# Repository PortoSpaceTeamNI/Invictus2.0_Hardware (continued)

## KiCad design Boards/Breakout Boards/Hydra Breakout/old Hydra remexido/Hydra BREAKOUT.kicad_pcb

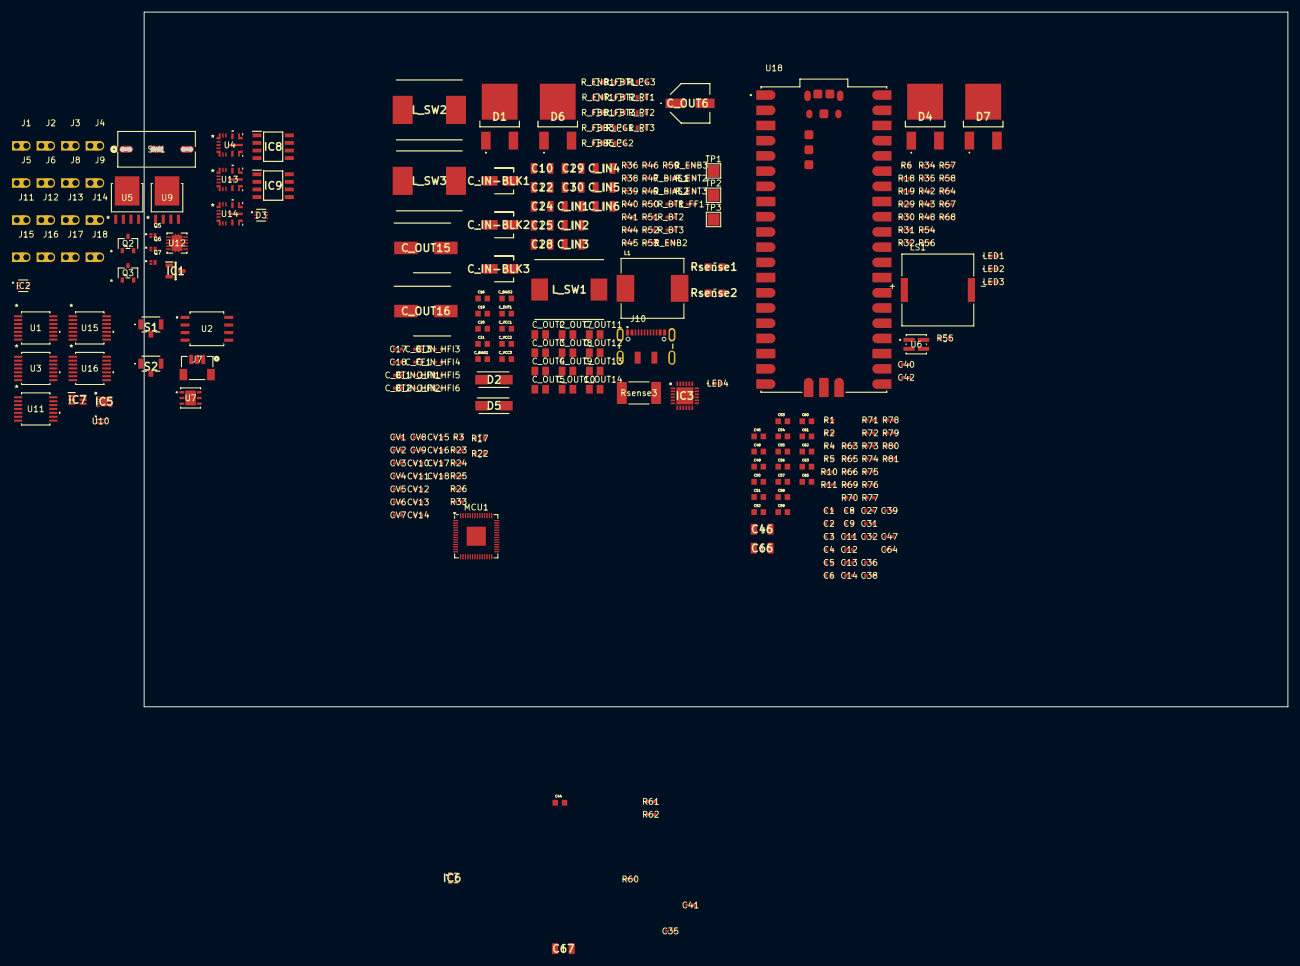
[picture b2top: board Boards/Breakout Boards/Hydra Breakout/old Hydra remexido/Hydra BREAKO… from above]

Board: 4 copper layers, 194.6 x 116.0 mm, 282 parts (0 on the bottom side), 160 nets, no tracks yet.

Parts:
C1, C3, C4, C5, C8, C9, C11, C13, C14, C17, C18, C27, C35, C36, C40, C41, C42, C47, C64: 100n; Capacitor_0402
C2, C6, C12, C31, C32, C39: 10n; Capacitor_0402
C10, C24, C25, C28: 2.2u; Capacitor_1206
C16, C19, C20, C21, C44, C45, C65: 1u; Capacitor_0603
C22, C46, C66, C67: 4.7u; Capacitor_1206
C29, C30: 470n; Capacitor_1206
C38: 100nF; Capacitor_0402
C48, C51, C53, C55, C60, C61, C62, C63: 22n; Capacitor_0603
C49, C50, C52, C54, C56, C57, C58, C59: 27n; Capacitor_0603
CV1, CV3, CV6, CV16, CV17: 1uF; Capacitor_0402
CV2, CV4, CV5, CV7, CV8, CV9, CV10, CV11, CV12, CV13, CV18: 100nF; Capacitor_0402
CV14, CV15: 4.7uF; Capacitor_0402
C_BIAS1, C_BIAS2: 1u; Capacitor_0603
C_BT1, C_BT2, C_BT3: 100n; Capacitor_0402
C_FF1: 22p; Capacitor_0402
C_IN1, C_IN2, C_IN3, C_IN4, C_IN5, C_IN6: 4.7u; Capacitor_1206
C_IN-BLK1, C_IN-BLK2, C_IN-BLK3: 10u; Capacitor_4mm
C_IN_HFI1, C_IN_HFI2, C_IN_HFI3, C_IN_HFI4, C_IN_HFI5, C_IN_HFI6: 100n; Capacitor_0402
C_OUT1: 1u; Capacitor_0603
C_OUT2, C_OUT3, C_OUT4, C_OUT5: 10u; Capacitor_0805
C_OUT6: 100u; Capacitor_6mm
C_OUT7, C_OUT8, C_OUT11, C_OUT12, C_OUT13, C_OUT14: 22u; Capacitor_0805
C_OUT9, C_OUT10: 47u; Capacitor_0805
C_OUT15: 560u; Capacitor_8mm
C_OUT16: 100u; Capacitor_8mm
C_VCC1, C_VCC2, C_VCC3: 1u; Capacitor_0603
D1, D6: RB095BGE; RD3P175SNFRATL
D2, D5: RSX301L; DIOM5026X220N
D3: SP3004-04XTG; SOT563_LTF
D4, D7: RB095BGE-30TL; RD3P175SNFRATL
IC1: BC846BLT1G; SOT96P237X111-3N
IC2: NSVT30010MXV6T1G; SOT-563_1P3X1P7_ONS
IC3: CYPD3177-24LQXQT; QFN50P400X400X60-25N-D
IC5: INA2181A4IDSQR; SON40P200X200X80-11N
IC6: PCA9306GM,125; PCA9570GMH
IC7: INA181A4QDCKRQ1; SOT65P210X110-6N
IC8, IC9: DMP2040USD-13; SOIC127P600X175-8N
J1, J2, J3, J4, J5, J6, J8, J9, J11, J12, J13, J14, J15, J16, J17, J18: Conn_01x01_Socket; Pico_01pin
J7: BM03B-SRSS-TBLFSN; CONN_BM03B-SRSS-TBLFSN_JST
J10: DX07S016JA1R1500; JAE_DX07S016JA1R1500
L1: 2.2u; IND_SPM10065VT-2R2M-D
LED1, LED2, LED3, LED4: VLMS1500-GS08; LED_00-GS08_VIS_RED
LS1: PKLCS1212E20A0-R1
L_SW1: 10u; Inductor_11.5x10
L_SW2, L_SW3: 15u; Inductor_10.1x10
MCU1: RP2040; QFN-56-1EP_7x7mm_P0.4mm_EP3.2x3.2mm
Q2, Q3: 2N7002H6327XTSA2; PG-SOT23-3-5_INF_MIN
Q5, Q6, Q7: BC857CMB_315; TRANS_PMZB550UNEYL
R1, R2, R4, R5, R10, R11, R23, R24, R29, R32, R34, R64, R67: 100; RES_0402
R3, R18, R19, R25, R26, R52, R53, R61, R62, R63, R65, R66, R69, R70, R71, R72, R73, R74, R75, R76, R77, R78, R79, R80, R81: 1k; RES_0402
R6, R30, R33, R48, R51, R68: 10k; RES_0402
R17, R22: 27; RES_0603
R31: 150; RES_0402
R35, R36, R38, R39, R40, R41, R43, R44, R45, R46, R57, R58: 2k; RES_0402
R42: 65; RES_0402
R47: DNP; RES_0402
R49, R50: 50k; RES_0402
R54: 320; RES_0402
R55: 120; RES_0603
R56: 500; RES_0402
R59: 95; RES_0402
R60: 200k; RES_0402
R_BIAS1, R_BIAS2: 5; RES_0402
R_BT1, R_BT2: 50; RES_0402
R_BT3: 100; RES_0402
R_ENB1: 100k; RES_0603
R_ENB2: 63k4; RES_0402
R_ENB3: 45k3; RES_0402
R_ENT1: 931k; RES_0603
R_ENT2: 590k; RES_0402
R_ENT3: 422k; RES_0402
R_FBB1: 8k66; RES_0603
R_FBB3: 12k7; RES_0603
R_FBB5: 22k1; RES_0603
R_FBT1, R_FBT2, R_FBT3: 100K; RES_0603
R_FF1: 1k; RES_0402
R_PG1, R_PG2, R_PG3: 100K; RES_0603
R_RT1, R_RT2, R_RT3: 33k2; RES_0603
Rsense1, Rsense2: 2.5m; RES_0805
Rsense3: 20m; RES_WSLP2512
S1, S2: TL1017AABF160QG
SW1: D2F-01-D; D2F-01-D_OMR
TP1, TP2, TP3: TestPoint; TestPoint_Pad_2.0x2.0mm
U1, U3, U11: MAX31856MUD+T; 21-0066J_14_MXM
U2: W25Q128JVSIQ TR; SOIC_208MIL_WIN
U4, U13, U14: LM61460AASQRJRRQ1; VQFN-HR14_RJR_TEX
U5, U9: SQJA36EP-T1_GE3; PowerPAK_SO-8L_3_VIS
U6: VLMKG3400-GS08; SMT_00-GS08_VIS
U7: ST1L05APU33R; DFN_5APU33R_STM
U10: STLM20DD9F; UDFN-4L_STM
U12: THVD2410VDRCR; VSON10_DRC_TEX
U15, U16: AD8040ARUZ; RU_14_ADI
U18: SC0915; MODULE_SC0915

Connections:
+3.3V: C3.2, C4.2, C8.2, C9.2, C13.2, C14.2, C17.1, C18.1, C19.1, C38.1, C41.1, C42.2, CV5.1, CV6.1, CV7.1, CV8.1, CV9.1, CV10.1, CV11.1, CV12.1, CV13.1, CV15.2, CV17.1, CV18.1, IC3.5 (ISNK_COARSE), IC3.23 (VDDD), IC6.2 (VREF1), MCU1.1 (IOVDD), MCU1.10 (IOVDD), MCU1.22 (IOVDD), MCU1.33 (IOVDD), MCU1.42 (IOVDD), MCU1.43 (ADC_AVDD), MCU1.44 (VREG_IN), MCU1.48 (USB_VDD), MCU1.49 (IOVDD), Q2.1 (G), Q3.1 (G), R3.1, R33.2, R39.1, R40.1, R41.1, R43.1, R44.2, R45.2, R47.2, R48.1, R58.1, U1.5 (AVDD), U1.8 (DVDD), U2.8 (VCC), U3.5 (AVDD), U3.8 (DVDD), U7.2 (V0), U10.4 (VCC), U11.5 (AVDD), U11.8 (DVDD), U12.1 (VIO)
+5V: C27.1, C36.1, C40.1, C44.1, C67.1, CV14.2, CV16.2, D3.5 (VCC), IC5.10 (VS), IC7.3 (VS), IC7.5 (IN-), IC9.5 (D2), IC9.6 (D2), LED1.2, LED2.2, LED3.2, LED4.2, LS1.P, R19.1, R35.1, R57.1, R60.2, R61.1, R62.1, Rsense3.2, SW1.2, U6.1 (C_RED), U6.3 (C_Green), U7.3 (V1), U12.10 (VCC)
+8.4V: C45.1, C46.1, C47.2, C64.2, C65.1, C66.1, IC5.8 (IN-2), J17.1, Rsense2.2, U15.4 (+VS), U16.4 (+VS)
+12V: D4.2, D7.2, IC5.2 (IN-1), J18.1, Rsense1.2
/1~DRDY THERMO: MCU1.9 (GPIO7), U1.7 (~DRDY)
/1~FAULT THERMO: MCU1.15 (GPIO12), Q5.1, U1.13 (~FAULT)
/2~DRDY THERMO: MCU1.27 (GPIO16), U11.7 (~DRDY)
/2~FAULT THERMO: MCU1.28 (GPIO17), Q6.1, U11.13 (~FAULT)
/3~DRDY THERMO: MCU1.29 (GPIO18), U3.7 (~DRDY)
/3~FAULT THERMO: MCU1.30 (GPIO19), Q7.1, U3.13 (~FAULT)
/ENABLE_RS: MCU1.8 (GPIO6), R30.1, U12.3 (DE), U12.4 (~RE)
/Green Status: IC2.2 (B2), MCU1.37 (GPIO25)
/MISO SPI: MCU1.13 (GPIO10), U1.11 (SDO), U3.11 (SDO), U11.11 (SDO)
/MOSI SPI: MCU1.14 (GPIO11), U1.12 (SDI), U3.12 (SDI), U11.12 (SDI)
/Main Solenoid Valve: D7.1, D7.3, J15.1, U9.5 (D)
/PCB Temperature Sense: MCU1.38 (GPIO26_ADC0), U10.1 (VOUT)
/Power Unit/DC.DC1 PGOOD: R_PG1.2, TP1.1, U14.5 (PGOOD)
/Power Unit/DC.DC1 VCC: C_VCC1.1, R_PG1.1, U14.2 (VCC)
/Power Unit/DC.DC2 PGOOD: C_BIAS1.2, R_PG2.2, TP2.1, U4.5 (PGOOD)
/Power Unit/DC.DC2 VCC: C_VCC2.1, R_PG2.1, U4.2 (VCC)
/Power Unit/DC.DC3 PGOOD: C_BIAS2.2, R_PG3.2, TP3.1, U13.5 (PGOOD)
/Power Unit/DC.DC3 VCC: C_VCC3.1, R_PG3.1, U13.2 (VCC)
/Power Unit/GPIO USB-C: IC3.8 (GPIO_1), MCU1.34 (GPIO22)
/Power Unit/PD ~INT USB-C: IC3.7 (HPI_INT), MCU1.35 (GPIO23)
/Power Unit/SCL I2C: IC3.13 (HPI_SCL), IC6.3 (SCL1), MCU1.18 (GPIO15), R45.1
/Power Unit/SDA I2C: IC3.12 (HPI_SDA), IC6.4 (SDA1), MCU1.17 (GPIO14), R44.1
/Power Unit/USB DN: D3.3 (IO2), J10.5 (D-), J10.8 (D-), R17.1
/Power Unit/USB DP: D3.6 (IO4), J10.6 (D+), J10.7 (D+), R22.1
/Power Unit/V1 DP: D6.2, IC5.3 (IN+1), Rsense1.1
/Power Unit/V2 DP: D1.2, IC5.7 (IN+2), Rsense2.1
/Power Unit/V3 DP: D5.1 (K), IC7.4 (IN+), Rsense3.1
/Purge Solenoid Valve: D4.1, D4.3, J13.1, U5.5 (D)
/Purge Valve Enable: MCU1.31 (GPIO20), R6.1, U5.4 (G)
/READ_RS: MCU1.6 (GPIO4), R48.2, U12.2 (R)
/RP2040 Standard/MCU SCLK SPI: MCU1.52 (QSPI_SCLK), U2.6 (CLK)
/RP2040 Standard/MCU SD0 SPI: MCU1.53 (QSPI_SD0), U2.5 (DI(IO0))
/RP2040 Standard/MCU SD1 SPI: MCU1.55 (QSPI_SD1), U2.2 (DO(IO1))
/RP2040 Standard/MCU SD2 SPI: MCU1.54 (QSPI_SD2), U2.3 (/WP(IO2))
/RP2040 Standard/MCU SD3 SPI: MCU1.51 (QSPI_SD3), U2.7 (/HOLD_/RESET)
/RP2040 Standard/MCU ~CS SPI: MCU1.56 (QSPI_SS), R26.2, U2.1 (/CS)
/RP2040 Standard/~RST: R25.1, S1.2 (NO)
/RP2040 Standard/~USB_BOOT: R26.1, S2.2 (NO)
/RS_DN: J8.1, R55.1, U12.9 (B)
/RS_DP: J9.1, R55.2, U12.8 (A)
/Red Status: IC2.5 (B1), MCU1.36 (GPIO24)
/SCK SPI: MCU1.11 (GPIO8), U1.10 (SCK), U3.10 (SCK), U11.10 (SCK)
/Sensor Unit/5V_Sense: IC7.6 (OUT), R70.1
/Sensor Unit/8.4V_Sense: IC5.9 (OUT2), R66.1
/Sensor Unit/12V_Sense: IC5.1 (OUT1), R63.1
/Sensor Unit/ADC1 Sense: C49.2, U15.1 (VOUT1), U15.2 (-IN1)
/Sensor Unit/ADC2 Sense: C50.2, U15.6 (-IN2), U15.7 (VOUT2)
/Sensor Unit/ADC3 Sense: C52.2, U15.8 (VOUT3), U15.9 (-IN3)
/Sensor Unit/ADC4 Sense: C54.2, U15.13 (-IN4), U15.14 (VOUT4)
/Sensor Unit/ADC5 Sense: C56.2, U16.1 (VOUT1), U16.2 (-IN1)
/Sensor Unit/ADC6 Sense: C57.2, U16.6 (-IN2), U16.7 (VOUT2)
/Sensor Unit/ADC7 Sense: C58.2, U16.8 (VOUT3), U16.9 (-IN3)
/Sensor Unit/ADC8 Sense: C59.2, U16.13 (-IN4), U16.14 (VOUT4)
/Sensor Unit/Clock I2C: IC6.6 (SCL2), R61.2
/Sensor Unit/Data I2C: IC6.5 (SDA2), R62.2
/Sensor Unit/THERMO1 DN: R2.2, U1.2 (BIAS)
/Sensor Unit/THERMO2 DN: R11.2, U11.2 (BIAS)
/Sensor Unit/THERMO3 DP: R5.2, U3.2 (BIAS)
/Servo_IN1 PWM: MCU1.4 (GPIO2), Q2.2 (S), R43.2
/Servo_IN2 PWM: MCU1.5 (GPIO3), Q3.2 (S), R58.2
/Servo_OUT1 PWM: J14.1, Q2.3 (D), R35.2
/Servo_OUT2 PWM: Q3.3 (D), R57.2
/Solenoid Valve Enable: MCU1.32 (GPIO21), R68.1, U9.4 (G)
/WRITE_RS: MCU1.7 (GPIO5), U12.5 (D)
/~CS THERMO1 SPI: MCU1.12 (GPIO9), U1.9 (~CS)
/~CS THERMO2 SPI: MCU1.16 (GPIO13), U11.9 (~CS)
/~CS THERMO3 SPI: MCU1.41 (GPIO29_ADC3), U3.9 (~CS)
GND: C2.2, C3.1, C4.1, C6.2, C8.1, C9.1, C12.2, C13.1, C14.1, C31.1, C32.1, C35.2, C39.1, C40.2, C41.2, C42.1, CV1.2, CV2.1, CV3.2, CV4.1, CV5.2, CV6.2, CV7.2, CV8.2, CV9.2, CV10.2, CV11.2, CV12.2, CV13.2, CV14.1, CV15.1, CV16.1, CV17.2, CV18.2, IC1.2 (E), IC2.3 (C1), IC2.6 (C2), IC6.1 (GND), J7.2, J12.1, MCU1.19 (TESTEN), MCU1.57 (GND), Q5.3, Q6.3, Q7.3, R6.2, R30.2, R31.1, R36.1, R38.2, R42.1, R46.2, R54.1, R56.1, R68.2, R_ENB1.1, R_ENB2.1, R_ENB3.1, S1.1 (COM), S1.G1, S2.1 (COM), S2.G1, SW1.1, U1.14 (DGND), U2.4 (GND), U3.14 (DGND), U5.1 (S), U5.2 (S), U5.3 (S), U7.6 (GND), U7.7 (GND), U9.1 (S), U9.2 (S), U9.3 (S), U11.14 (DGND), U12.6 (GND), U12.11 (EPAD), U14.1 (BIAS)
GNDA: C16.2, C17.2, C18.2, C19.2, C22.2, C27.2, C36.2, C38.2, C44.2, C45.2, C46.2, C47.1, C48.2, C51.2, C53.2, C55.2, C60.2, C61.2, C62.2, C63.2, C64.1, C65.2, C66.2, C67.2, C_IN1.2, C_IN2.2, C_IN3.2, C_IN4.2, C_IN5.2, C_IN6.2, C_IN-BLK1.2, C_IN-BLK2.2, C_IN-BLK3.2, C_IN_HFI1.2, C_IN_HFI2.2, C_IN_HFI3.2, C_IN_HFI4.2, C_IN_HFI5.2, C_IN_HFI6.2, C_OUT1.2, C_OUT2.2, C_OUT3.2, C_OUT4.2, C_OUT5.2, C_OUT6.2, C_OUT7.2, C_OUT8.2, C_OUT9.2, C_OUT10.2, C_OUT11.2, C_OUT12.2, C_OUT13.2, C_OUT14.2, C_OUT15.2, C_OUT16.2, C_VCC1.2, C_VCC2.2, C_VCC3.2, D3.2 (GND), IC3.19 (GND), IC3.22 (VSS), IC3.25 (EP), IC5.4 (GND_1), IC5.5 (REF1), IC5.6 (REF2), IC5.11 (GND_2), IC7.1 (REF), IC7.2 (GND), J10.1 (GND), J10.12 (GND), R_FBB1.1, R_FBB3.1, R_FBB5.1, R_RT1.1, R_RT2.1, R_RT3.1, U1.1 (AGND), U3.1 (AGND), U4.3 (AGND), U4.9 (PGND1), U4.11 (PGND2), U10.3 (GND), U11.1 (AGND), U13.3 (AGND), U13.9 (PGND1), U13.11 (PGND2), U14.3 (AGND), U14.9 (PGND1), U14.11 (PGND2), U15.11 (-VS), U16.11 (-VS)
GNDPWR: C10.2, C24.2, C25.2, C28.2, C29.2, C30.2
unnamed: C49.1, R63.2, R65.1
unnamed: C50.1, R66.2, R69.1
unnamed: C52.1, R70.2, R71.1
unnamed: C54.1, R72.2, R73.1
unnamed: C56.1, R74.2, R78.1
unnamed: C57.1, R75.2, R79.1
unnamed: C58.1, R76.2, R80.1
unnamed: C59.1, R77.2, R81.1
unnamed: C_FF1.1, R_FF1.2
unnamed: C_OUT1.1, C_OUT2.1, C_OUT3.1, C_OUT4.1, C_OUT5.1, C_OUT6.1, D6.1, D6.3, L_SW1.2, R_FBT1.1
unnamed: C_OUT7.1, C_OUT8.1, C_OUT9.1, C_OUT10.1, C_OUT16.1, D1.1, D1.3, L_SW2.2, R_BIAS1.2, R_FBT2.1
unnamed: C20.2, C21.2, D2.2 (A), IC8.2 (G1), IC8.4 (G2), R49.2, R51.2, R52.2
unnamed: D2.1 (K), IC8.1 (S1), IC8.3 (S2), R49.1
unnamed: D3.1 (IO1), IC3.15 (CC1), J10.3 (CC1)
unnamed: D3.4 (IO3), IC3.14 (CC2), J10.9 (CC2)
unnamed: C_OUT11.1, C_OUT12.1, C_OUT13.1, C_OUT14.1, C_OUT15.1, D5.2 (A), L_SW3.2, R_BIAS2.2, R_FBT3.1, R_FF1.1
unnamed: IC1.1 (B), R18.1
unnamed: IC1.3 (C), LS1.N, R19.2
unnamed: IC2.4 (E1), R67.1
unnamed: IC2.1 (E2), R64.2
unnamed: IC3.10 (FLIP), R41.2
unnamed: IC3.6 (ISNK_FINE), R46.1, R47.1
unnamed: IC3.4 (SAFE_PWR_EN), R53.1
unnamed: IC3.3 (VBUS_FET_EN), R52.1
unnamed: IC3.2 (VBUS_MAX), R36.2, R39.2
unnamed: IC3.1 (VBUS_MIN), R38.1, R40.2
unnamed: C16.1, IC3.24 (VCCD)
unnamed: C35.1, IC6.7 (VREF2), IC6.8 (EN), R60.1
unnamed: IC9.2 (G1), IC9.4 (G2), R50.2, R53.2
unnamed: IC9.1 (S1), IC9.3 (S2)
unnamed: J7.1, R23.1
unnamed: J7.3, R24.1
unnamed: LED1.1, R29.2
unnamed: LED2.1, R32.2
unnamed: LED3.1, R34.2
unnamed: CV1.1, MCU1.26 (RUN), R3.2, R25.2
unnamed: MCU1.24 (SWCLK), R23.2
unnamed: MCU1.25 (SWD), R24.2
unnamed: MCU1.46 (USB_DM), R22.2
unnamed: MCU1.47 (USB_DP), R17.2
unnamed: CV2.2, CV3.1, CV4.2, MCU1.23 (DVDD), MCU1.45 (VREG_VOUT), MCU1.50 (DVDD)
unnamed: Q5.2, R29.1
unnamed: Q6.2, R32.1
unnamed: Q7.2, R34.1
unnamed: C1.1, C31.2, R1.1, U1.4 (T+)
unnamed: C1.2, C2.1, R2.1, U1.3 (T-)
unnamed: C5.1, C32.2, R4.1, U3.4 (T+)
unnamed: C5.2, C6.1, R5.1, U3.3 (T-)
unnamed: C_BIAS1.1, R_BIAS1.1, U4.1 (BIAS)
unnamed: C_BT2.2, R_BT2.1, U4.14 (CBOOT)
unnamed: R_ENB2.2, R_ENT2.1, U4.7 (EN/SYNC)
unnamed: R_FBB3.2, R_FBT2.2, U4.4 (FB)
unnamed: R_BT2.2, U4.13 (RBOOT)
unnamed: R_RT2.2, U4.6 (RT)
unnamed: C_BT2.1, L_SW2.1, U4.10 (SW)
unnamed: R64.1, U6.2 (A_Green)
unnamed: R67.2, U6.4 (A_Red)
unnamed: C11.1, C39.2, R10.1, U11.4 (T+)
unnamed: C11.2, C12.1, R11.1, U11.3 (T-)
unnamed: SW1.3, U12.7 (SLR)
unnamed: C_BIAS2.1, R_BIAS2.1, U13.1 (BIAS)
unnamed: C_BT3.2, R_BT3.1, U13.14 (CBOOT)
unnamed: R_ENB3.2, R_ENT3.1, U13.7 (EN/SYNC)
unnamed: C_FF1.2, R_FBB5.2, R_FBT3.2, U13.4 (FB)
unnamed: R_BT3.2, U13.13 (RBOOT)
unnamed: R_RT3.2, U13.6 (RT)
unnamed: C_BT3.1, L_SW3.1, U13.10 (SW)
unnamed: C_BT1.2, R_BT1.1, U14.14 (CBOOT)
unnamed: R_ENB1.2, R_ENT1.1, U14.7 (EN/SYNC)
unnamed: R_FBB1.2, R_FBT1.2, U14.4 (FB)
unnamed: R_BT1.2, U14.13 (RBOOT)
unnamed: R_RT1.2, U14.6 (RT)
unnamed: C_BT1.1, L_SW1.1, U14.10 (SW)
unnamed: C48.1, R65.2, U15.3 (+IN1)
unnamed: C51.1, R69.2, U15.5 (+IN2)
unnamed: C53.1, R71.2, U15.10 (+IN3)
unnamed: C55.1, R73.2, U15.12 (+IN4)
unnamed: C60.1, R78.2, U16.3 (+IN1)
unnamed: C61.1, R79.2, U16.5 (+IN2)
unnamed: C62.1, R80.2, U16.10 (+IN3)
unnamed: C63.1, R81.2, U16.12 (+IN4)
unnamed: U18.3 (GND), U18.8 (GND), U18.13 (GND), U18.18 (GND), U18.23 (GND), U18.28 (GND), U18.38 (GND), U18.D2 (GND)
unnamed: U18.A (USB_SHIELD), U18.B (USB_SHIELD), U18.C (USB_SHIELD), U18.D (USB_SHIELD)
VBAT: C10.1, C20.1, C24.1, IC3.11 (VDC_OUT), IC8.7 (D1), IC8.8 (D1), J11.1, L1.1
VBUS: C21.1, C22.1, C_IN1.1, C_IN_HFI1.1, IC3.18 (VBUS_IN), IC8.5 (D2), IC8.6 (D2), IC9.7 (D1), IC9.8 (D1), J10.2 (VBUS), J10.11 (VBUS), R50.1, R51.1, R_ENT1.2, U14.8 (VIN1)
VDC: C25.1, C28.1, C29.1, C30.1, C_IN2.1, C_IN3.1, C_IN4.1, C_IN5.1, C_IN6.1, C_IN-BLK1.1, C_IN-BLK2.1, C_IN-BLK3.1, C_IN_HFI2.1, C_IN_HFI3.1, C_IN_HFI4.1, C_IN_HFI5.1, C_IN_HFI6.1, L1.2, R_ENT2.2, R_ENT3.2, U4.8 (VIN1), U4.12 (VIN2), U13.8 (VIN1), U13.12 (VIN2), U14.12 (VIN2)

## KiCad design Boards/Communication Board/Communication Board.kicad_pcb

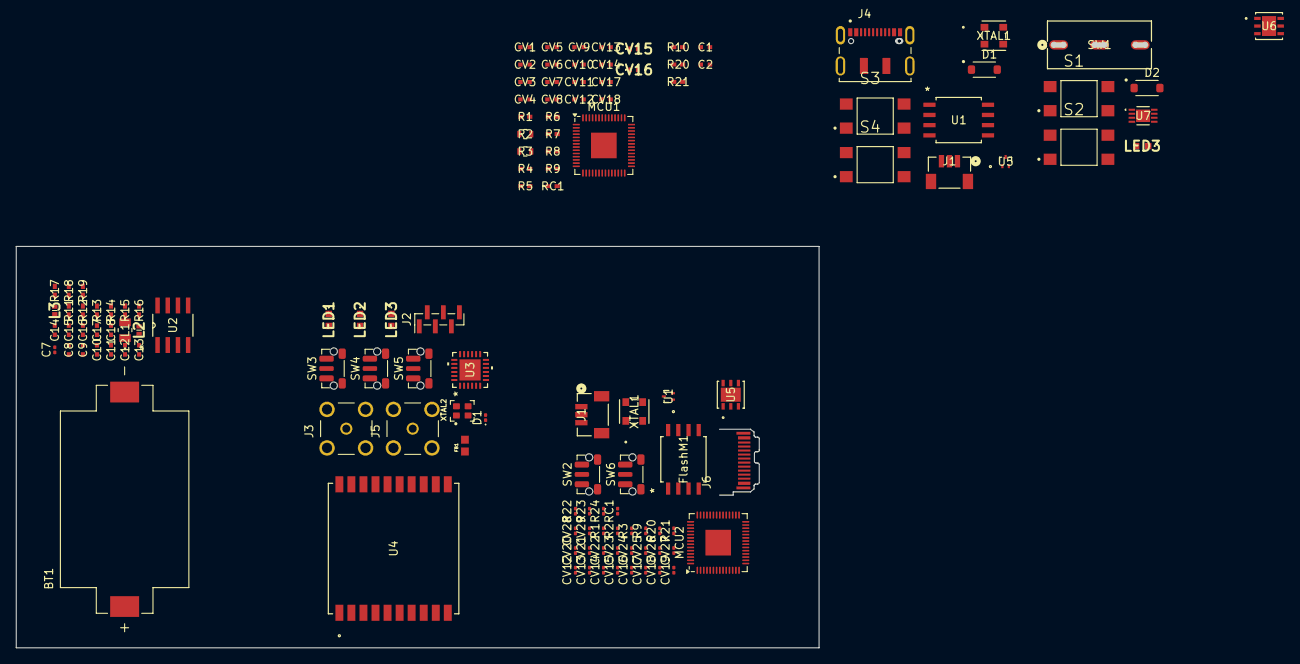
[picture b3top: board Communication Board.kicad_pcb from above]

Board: 4 copper layers, 140.6 x 75.9 mm, 126 parts (0 on the bottom side), 87 nets, no tracks yet.

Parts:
BT1: 1060TR; BAT_1060TR
C1, C2, C9: 10nF; CAP_GCM155_MUR
C7: 10nF; C_0201_0603Metric
C8, C12, C13: 100nF; CAP_GCM155_MUR
C10: 470nF; CAP_GCM155_MUR
C11: 1uF; CAP_GCM155_MUR
C14: 0.8pF; CAP_GCM155_MUR
C15, C17: 1.2pF; CAP_GCM155_MUR
C16: 0.5pF; CAP_GCM155_MUR
C18: 100pF; CAP_GCM155_MUR
CV1, CV3, CV6, CV13#2, CV17: 1uF; CAP_GCM155_MUR
CV2, CV4, CV5, CV7, CV8, CV9, CV10, CV11, CV12, CV14, CV18#2: 100nF; CAP_GCM155_MUR
CV12#2, CV14#2, CV17#2, CV24, CV28: 1uF; C_0201_0603Metric
CV13, CV15#2, CV16#2, CV18, CV19, CV20, CV21, CV22, CV23, CV25, CV29: 100nF; C_0201_0603Metric
CV15, CV16: 4.7uF; GRM15x
CV26, CV27: 4.7uF; C_0201_0603Metric
D1, D2: PMEG2010ER; SODFL3517X110N
D1#2: D; D_0201_0603Metric
FB1: FerriteBead; BEADC1608X95N
FlashM1: W25Q128JVSIQ_TR; SOIC_208MIL_WIN
J1, J1#2: BM03B-SRSS-TBLFSN; CONN_BM03B-SRSS-TBLFSN_JST
J2: Conn_01x06_Pin; PinHeader_1x06_P1.00mm_Vertical_SMD_Pin1Left
J3, J5: SMA_CONNECTOR; LPRS_SMA_CONNECTOR
J4: DX07S016JA1R1500; JAE_DX07S016JA1R1500
J6: USB_C; USB_C_Plug_JAE_DX07P024AJ1
L1: 15uH; IND_2012_TDK
L2: 3nH; LQW15CNR20J00B
L3: 2.5nH; LQW15CNR20J00B
LED1, LED2, LED3, LED3#2: HSMH-H191; HSMHH191
MCU1, MCU2: RP2040; QFN-56-1EP_7x7mm_P0.4mm_EP3.2x3.2mm
R1, R6, R8, R11, R16: 1k; RC0402N_VIS
R1#2, R21#2, R23: 1k; R_0201_0603Metric
R2, R3#2: 27; R_0201_0603Metric
R2#2, R3: 27; RES_R0603_ROM
R4, R5: 100; RC0402N_VIS
R7, R14: 10k; RC0402N_VIS
R9, R20: 100; R_0201_0603Metric
R9#2: 5k1; RC0402N_VIS
R10, R20#2, R21: 2k; RC0402N_VIS
R12: 470; RC0402N_VIS
R13, R18: 47; RC0402N_VIS
R15, R17: 10K; RC0402N_VIS
R19: 130; RC0402N_VIS
R22: 10k; R_0201_0603Metric
R24: 5k1; R_0201_0603Metric
RC1: 5k1; RC0402N_VIS
RC1#2: 5k1; R_0201_0603Metric
S1, S2, S3, S4: TL3305CF160QG; SW_TL3305CF160QG
SW1: D2F-01-D; D2F-01-D_OMR
SW2, SW3, SW4, SW5, SW6: SW_Push; SW_Push_1P1T-MP_NO_Horizontal_Alps_SKRTLAE010
U1: W25Q128JVSIQ TR; SOIC_208MIL_WIN
U1#2, U5: ESD7L5.0DT5G; SOT-723_0P85X1P25_ONS
U2: TPS1120DR; D8
U3: SX1280IMLTRT; QFN24_4X4_SEM
U4: CD-PA1616; CD-PA1616D_ADA
U5#2, U6: ST1L05APU33R; DFN_5APU33R_STM
U7: MCP9808T-E/MC; DFN8_2x3MC_MCH
XTAL1, XTAL1#2: ASE-12.000MHZ-LC-T; ASE-3.2X2.5_ABR
XTAL2: NX2016SA-52MHZ-EXS00A-CS07103; OSCCC200X160X50N

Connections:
+3.3V: C2.1, C8.1, C13.1, CV5.1, CV6.1, CV7.1, CV8.1, CV9.1, CV10.1, CV11.1, CV12.1, CV13#2.1, CV14.1, CV16.2, CV16#2.1, CV17#2.1, CV18.1, CV18#2.1, CV19.1, CV20.1, CV21.1, CV22.1, CV23.1, CV24.1, CV25.1, CV27.2, CV29.1, FB1.1, FlashM1.8 (VCC), MCU1.1 (IOVDD), MCU1.10 (IOVDD), MCU1.22 (IOVDD), MCU1.33 (IOVDD), MCU1.42 (IOVDD), MCU1.43 (ADC_AVDD), MCU1.44 (VREG_IN), MCU1.48 (USB_VDD), MCU1.49 (IOVDD), MCU2.1 (IOVDD), MCU2.10 (IOVDD), MCU2.22 (IOVDD), MCU2.33 (IOVDD), MCU2.42 (IOVDD), MCU2.43 (ADC_AVDD), MCU2.44 (VREG_IN), MCU2.48 (USB_VDD), MCU2.49 (IOVDD), R1.1, R1#2.1, R7.2, R10.1, R13.1, R15.2, R17.2, R18.2, R20#2.1, R21.1, R22.2, U1.8 (VCC), U3.15 (VBAT), U5#2.2 (V0), U6.2 (V0), U7.8 (VDD), XTAL1.4 (VDD), XTAL1#2.4 (VDD)
/GPS 1PPS: MCU1.5 (GPIO3), MCU2.5 (GPIO3), U4.13 (1PPS)
/GPS I2C SCL: MCU1.18 (GPIO15), MCU2.18 (GPIO15), R17.1, U4.14 (RX1(I2C_SCL))
/GPS I2C SDA: MCU1.17 (GPIO14), MCU2.17 (GPIO14), R15.1, U4.15 (TX1(I2C_SDA))
/GPS UART RX: MCU1.3 (GPIO1), MCU2.3 (GPIO1), U4.10 (RX0)
/GPS UART TX: MCU1.2 (GPIO0), MCU2.2 (GPIO0), U4.9 (TX0)
/GPS VBACKUP: SW1.3, SW5.1, U4.4 (VBACKUP)
/OBC UART CTS: J2.2, MCU1.8 (GPIO6), MCU2.8 (GPIO6)
/OBC UART RTS: J2.5, MCU1.9 (GPIO7), MCU2.9 (GPIO7)
/OBC UART RX: J2.4, MCU1.7 (GPIO5), MCU2.7 (GPIO5)
/OBC UART TX: J2.3, MCU1.6 (GPIO4), MCU2.6 (GPIO4)
/RP2040/GP8/SPI1 MISO: MCU1.11 (GPIO8), MCU2.11 (GPIO8)
/RP2040/GP10/SPI1 SCK: MCU1.13 (GPIO10), MCU2.13 (GPIO10)
/RP2040/GP11/SPI1 MOSI: MCU1.14 (GPIO11), MCU2.14 (GPIO11)
/RP2040/GP25/PWM4 B: MCU1.37 (GPIO25), MCU2.37 (GPIO25), R19.2
/RP2040/GP26_ADC0: MCU1.38 (GPIO26_ADC0), MCU2.38 (GPIO26_ADC0)
/RP2040/GP27_ADC1: MCU1.39 (GPIO27_ADC1), MCU2.39 (GPIO27_ADC1)
/RP2040/GP28_ADC2: MCU1.40 (GPIO28_ADC2), MCU2.40 (GPIO28_ADC2)
/RP2040/GP29_ADC3: MCU1.41 (GPIO29_ADC3), MCU2.41 (GPIO29_ADC3)
/RP2040/MCU QSPI_SCLK: FlashM1.6 (CLK), MCU1.52 (QSPI_SCLK), MCU2.52 (QSPI_SCLK), U1.6 (CLK)
/RP2040/MCU QSPI_SD0: FlashM1.5 (DI(IO0)), MCU1.53 (QSPI_SD0), MCU2.53 (QSPI_SD0), U1.5 (DI(IO0))
/RP2040/MCU QSPI_SD1: FlashM1.2 (DO(IO1)), MCU1.55 (QSPI_SD1), MCU2.55 (QSPI_SD1), U1.2 (DO(IO1))
/RP2040/MCU QSPI_SD2: FlashM1.3 (/WP(IO2)), MCU1.54 (QSPI_SD2), MCU2.54 (QSPI_SD2), U1.3 (/WP(IO2))
/RP2040/MCU QSPI_SD3: FlashM1.7 (/HOLD_/RESET), MCU1.51 (QSPI_SD3), MCU2.51 (QSPI_SD3), U1.7 (/HOLD_/RESET)
/RP2040/MCU QSPI_SS: FlashM1.1 (/CS), MCU1.56 (QSPI_SS), MCU2.56 (QSPI_SS), R8.2, R23.2, U1.1 (/CS)
/RP2040/USB_DM: J4.5 (D-), J4.8 (D-), J6.A7 (D-), J6.B7 (D-), R3.1, R3#2.1, U1#2.1, U5.1
/RP2040/USB_DP: J4.6 (D+), J4.7 (D+), J6.A6 (D+), J6.B6 (D+), R2.1, R2#2.1, U1#2.2, U5.2
/RP2040/~RST: R6.1, R21#2.1, S3.4, SW2.2
/RP2040/~USB_BOOT: R8.1, R23.1, S4.4, SW6.2
/SX1280 BUSY: MCU1.31 (GPIO20), MCU2.31 (GPIO20), U3.7 (BUSY)
/SX1280 DIO1: MCU1.32 (GPIO21), MCU2.32 (GPIO21), U3.8 (DIO1)
/SX1280 DIO2: MCU1.34 (GPIO22), MCU2.34 (GPIO22), U3.9 (DIO2)
/SX1280 DIO3: MCU1.35 (GPIO23), MCU2.35 (GPIO23), U3.10 (DIO3)
/SX1280 SPI MISO: MCU1.27 (GPIO16), MCU2.27 (GPIO16), U3.16 (MISO_TX)
/SX1280 SPI MOSI: MCU1.30 (GPIO19), MCU2.30 (GPIO19), U3.17 (MOSI_RX)
/SX1280 SPI SCK: MCU1.29 (GPIO18), MCU2.29 (GPIO18), U3.18 (SCK_RTSN)
/SX1280 SPI ~CS: MCU1.28 (GPIO17), MCU2.28 (GPIO17), U2.2 (1GATE), U3.19 (NSS_CTS)
/SX1280 XTA: U3.4 (XTA), XTAL2.3
/SX1280 XTB: U3.6 (XTB), XTAL2.1
/SX1280 ~RST: MCU1.12 (GPIO9), MCU2.12 (GPIO9), R16.2, U3.3 (NRESET)
/TEMP ALERT: MCU1.36 (GPIO24), R10.2, U7.3 (ALERT)
/TEMP SDA I2C: MCU1.15 (GPIO12), R21.2, U7.1 (SDA)
/TEMP SDL I2C: MCU1.16 (GPIO13), R20#2.2, U7.2 (SCL)
/V_IN: CV15.2, CV17.2, CV26.2, CV28.2, D1.C, J2.1, J6.A4 (VBUS), J6.A9 (VBUS), J6.B4 (VBUS), J6.B9 (VBUS), U5#2.3 (V1), U6.3 (V1)
CRYSTAL: MCU1.20 (XIN), MCU2.20 (XIN), XTAL1.3 (OUTPUT), XTAL1#2.3 (OUTPUT)
GND: BT1.N, C1.2, C2.2, C7.2, C8.2, C9.2, C10.2, C11.2, C12.2, C13.2, C14.2, C15.2, C17.2, CV1.2, CV2.1, CV3.2, CV4.1, CV5.2, CV6.2, CV7.2, CV8.2, CV9.2, CV10.2, CV11.2, CV12.2, CV12#2.2, CV13.1, CV13#2.2, CV14.2, CV14#2.2, CV15.1, CV15#2.1, CV16.1, CV16#2.2, CV17.1, CV17#2.2, CV18.2, CV18#2.2, CV19.2, CV20.2, CV21.2, CV22.2, CV23.2, CV24.2, CV25.2, CV26.1, CV27.1, CV28.1, CV29.2, FlashM1.4 (GND), J1.2, J1#2.2, J2.6, J3.G1, J3.G2, J3.G3, J3.G4, J4.1 (GND), J4.12 (GND), J5.G1, J5.G2, J5.G3, J5.G4, J6.A1 (GND), J6.A12 (GND), J6.B1 (GND), J6.B12 (GND), LED1.1 (K), LED2.1 (K), LED3#2.1 (K), MCU1.19 (TESTEN), MCU1.57 (GND), MCU2.19 (TESTEN), MCU2.57 (GND), R9#2.1, R24.1, RC1.1, RC1#2.1, S1.2, S2.2, S3.2, S4.2, SW2.1, SW3.1, SW4.1, SW6.1, U1.4 (GND), U1#2.3, U3.5 (GND), U3.13 (GND), U3.20 (GND), U3.21 (GND), U3.23 (GND), U3.24 (GND), U3.25 (GND), U4.3 (GND), U4.8 (GND), U4.12 (GND), U4.19 (GND), U5.3, U5#2.6 (GND), U5#2.7 (GND), U6.6 (GND), U6.7 (GND), U7.4 (GND), U7.5 (A2), U7.6 (A1), U7.7 (A0), U7.9 (EPAD), XTAL1.2 (GND/CASE), XTAL1#2.2 (GND/CASE), XTAL2.2 (GND), XTAL2.4 (GND__1)
unnamed: BT1.P, D2.A
unnamed: C15.1, C16.2, L2.2, L3.1
unnamed: C16.1, C17.1, C18.2, L3.2
unnamed: C18.1, J3.1
unnamed: D1#2.1 (K), SW5.2
unnamed: D1.A, J4.2 (VBUS), J4.11 (VBUS)
unnamed: D2.C, SW1.1
unnamed: J1.1, J1#2.1, R5.1, R9.1
unnamed: J1.3, J1#2.3, R4.1, R20.1
unnamed: J4.3 (CC1), RC1.2
unnamed: J4.9 (CC2), R9#2.2
unnamed: J6.A5 (CC1), R24.2
unnamed: J6.B5 (CC2), RC1#2.2
unnamed: LED1.2 (A), R12.1
unnamed: LED2.2 (A), R19.1
unnamed: LED3.2 (A), LED3#2.2 (A), U2.7 (1DRAIN), U2.8 (1DRAIN)
unnamed: CV1.1, MCU1.26 (RUN), R1.2, R6.2
unnamed: MCU1.24 (SWCLK), R4.2
unnamed: MCU1.25 (SWD), R5.2
unnamed: MCU1.46 (USB_DM), R3.2
unnamed: MCU1.47 (USB_DP), R2#2.2
unnamed: CV2.2, CV3.1, CV4.2, MCU1.23 (DVDD), MCU1.45 (VREG_VOUT), MCU1.50 (DVDD)
unnamed: CV12#2.1, MCU2.26 (RUN), R1#2.2, R21#2.2
unnamed: MCU2.24 (SWCLK), R9.2
unnamed: MCU2.25 (SWD), R20.2
unnamed: MCU2.46 (USB_DM), R3#2.2
unnamed: MCU2.47 (USB_DP), R2.2
unnamed: CV13.2, CV14#2.1, CV15#2.2, MCU2.23 (DVDD), MCU2.45 (VREG_VOUT), MCU2.50 (DVDD)
unnamed: R11.1, S2.4, SW3.2
unnamed: R16.1, S1.4, SW4.2
unnamed: R18.1, U2.1 (1SOURCE)
unnamed: C1.1, C7.1, C10.1, L1.1, U3.2 (VDD_INN), U3.12 (DCC_FB)
unnamed: L1.2, U3.14 (DCC_SW)
unnamed: C14.1, L2.1, U3.22 (RFIO)
unnamed: R13.2, U3.11 (VBAT_IO)
unnamed: C9.1, U3.1 (VR_PA)
unnamed: R12.2, U4.5 (3D-FIX)
unnamed: J5.1, U4.11 (EX_ANT)
unnamed: R11.2, R14.1, U4.2 (NRESET)
unnamed: C11.1, C12.1, FB1.2, R14.2, U4.1 (VCC)
unnamed: R7.1, R22.1, XTAL1.1 (TRI-STATE(STBY)), XTAL1#2.1 (TRI-STATE(STBY))
